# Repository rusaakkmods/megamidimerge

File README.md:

# rusaaKKMODS Megamidi Merge
================

A MIDI merge project for Arduino.

## Overview
-----------

This project is designed to merge MIDI input from multiple sources, calculate beats per minute (BPM), and update clock resolution as needed.

### Features
------------

* Merges MIDI input from two sources (MIDI-1 and MIDI-2)
* Calculates BPM from MIDI clock messages
* Updates clock resolution based on user input
* Displays current BPM, clock resolution, and master clock source on an OLED display

### Functions
-------------

* `initMidi()`: Initializes MIDI input and output interfaces.
* `calculateBPM()`: Calculates the current BPM from MIDI clock messages.
* `changeClockResolution()`: Updates the clock resolution based on user input.
* `readMidiInput()`: Reads and processes MIDI input from both sources.
* `printDisplay()`: Prints the current display information, including master clock source, BPM, and clock resolution.
* `isMasterInput1()`: Checks if the master clock source is set to MIDI-1.
* `loop()`: The main loop function that updates BPM, checks for user input, and reads MIDI input.

### Dependencies
------------

* Arduino library (for `millis()` and `digitalRead()` functions)
* MIDI library (for MIDI input and output handling)

### Hardware Requirements
----------------------

* Arduino board (e.g. Arduino Mega)
* MIDI input and output interfaces
* OLED display
* Push button for changing clock resolution

### Usage
-----

1. Upload the sketch to the Arduino board.
2. Connect the MIDI input and output interfaces to the board.
3. Connect the OLED display to the board.
4. Press the push button to change the clock resolution.

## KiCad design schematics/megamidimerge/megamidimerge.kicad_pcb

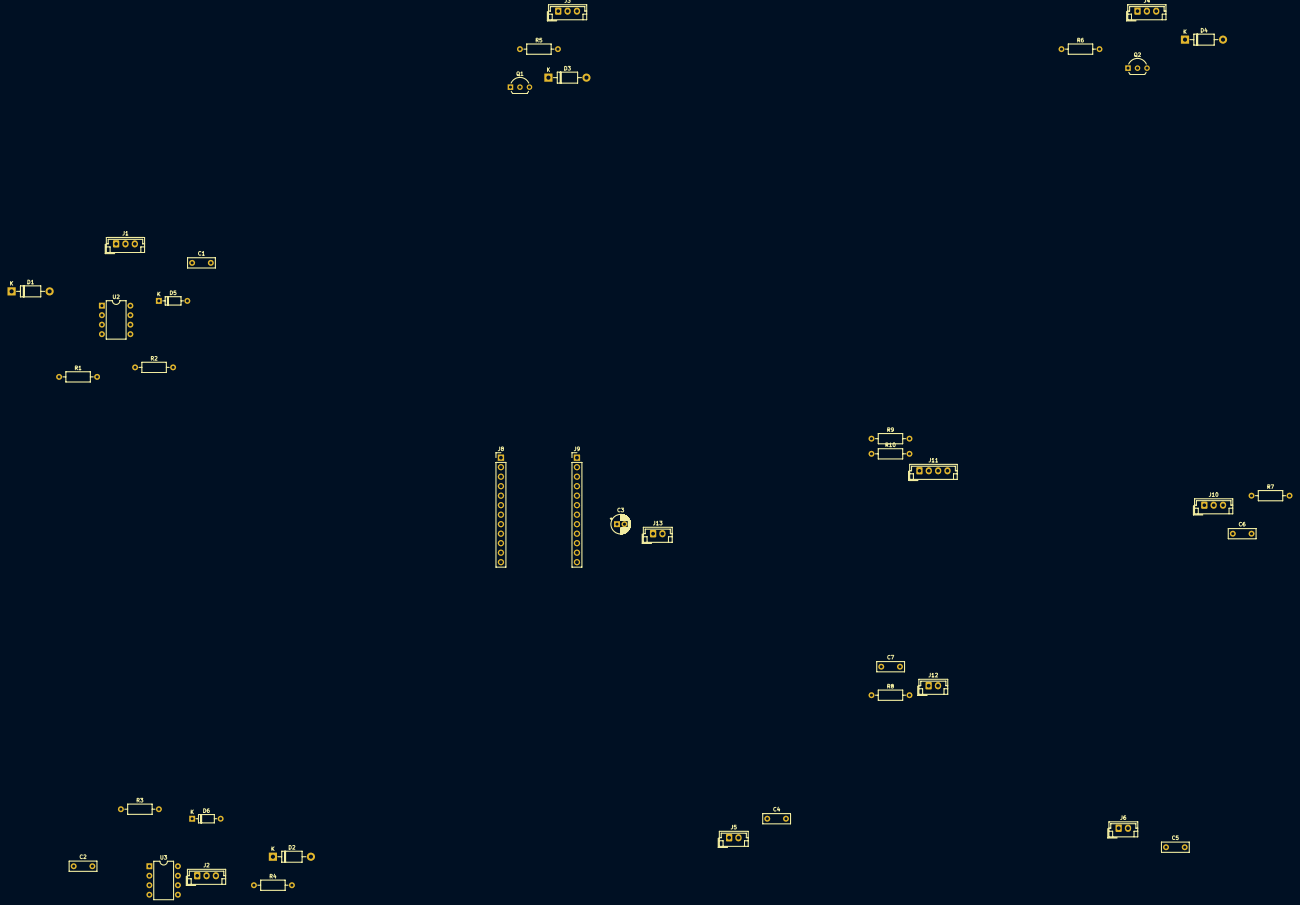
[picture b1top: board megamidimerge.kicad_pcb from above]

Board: 2 copper layers, 39 parts (0 on the bottom side), 24 nets, no tracks yet.

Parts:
C1, C2: 0.1uF; C_Rect_L7.2mm_W2.5mm_P5.00mm_FKS2_FKP2_MKS2_MKP2
C3: 10uF; CP_Radial_D5.0mm_P2.00mm
C4, C5, C6, C7: 10nF; C_Rect_L7.2mm_W2.5mm_P5.00mm_FKS2_FKP2_MKS2_MKP2
D1, D2, D3, D4: 1N5819; D_DO-41_SOD81_P10.16mm_Horizontal
D5, D6: 5.1V; D_DO-35_SOD27_P7.62mm_Horizontal
J1: MIDI IN 1; JST_EH_B3B-EH-A_1x03_P2.50mm_Vertical
J2: MIDI IN 2; JST_EH_B3B-EH-A_1x03_P2.50mm_Vertical
J3: MIDI OUT 1; JST_EH_B3B-EH-A_1x03_P2.50mm_Vertical
J4: MIDI OUT 2; JST_EH_B3B-EH-A_1x03_P2.50mm_Vertical
J5: CLOCK OUT 1; JST_EH_B2B-EH-A_1x02_P2.50mm_Vertical
J6: CLOCK OUT 2; JST_EH_B2B-EH-A_1x02_P2.50mm_Vertical
J8: LEFT; PinHeader_1x12_P2.54mm_Vertical
J9: RIGHT; PinHeader_1x12_P2.54mm_Vertical
J10: SWITCH MASTER; JST_EH_B3B-EH-A_1x03_P2.50mm_Vertical
J11: LCD; JST_EH_B4B-EH-A_1x04_P2.50mm_Vertical
J12: RESOLUTION; JST_EH_B2B-EH-A_1x02_P2.50mm_Vertical
J13: DC; JST_EH_B2B-EH-A_1x02_P2.50mm_Vertical
Q1, Q2: 2N2222; TO-92L_Inline_Wide
R1, R3, R5, R6: 220R; R_Axial_DIN0207_L6.3mm_D2.5mm_P10.16mm_Horizontal
R2, R4, R9, R10: 4.7K; R_Axial_DIN0207_L6.3mm_D2.5mm_P10.16mm_Horizontal
R7, R8: 10K; R_Axial_DIN0207_L6.3mm_D2.5mm_P10.16mm_Horizontal
U2, U3: 6N137; DIP-8_W7.62mm

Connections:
CLK1: C4.2, J5.2, J8.9
CLK2: C5.2, J6.2, J8.11
CPR: C7.1, J8.8, J12.1, R8.2
CSW: C6.1, J8.7, J10.2, R7.2
GND: C1.2, C2.2, C3.2, C4.1, C5.1, C6.2, C7.2, D3.2 (A), D4.2 (A), J1.3, J2.3, J3.3, J4.3, J5.1, J6.1, J8.3, J8.4, J9.2, J10.3, J11.1, J12.2, J13.2, Q1.3 (E), Q2.3 (E), R7.1, R8.1, U2.5 (GND), U3.5 (GND)
IN1: J8.2, R2.1, U2.6 (VO)
IN2: J8.10, R4.1, U3.6 (VO)
unnamed: D1.2 (A), J1.2, U2.3 (C)
unnamed: D1.1 (K), R1.2, U2.2 (A)
unnamed: D2.2 (A), J2.2, U3.3 (C)
unnamed: D2.1 (K), R3.2, U3.2 (A)
unnamed: D3.1 (K), J3.2, Q1.1 (C)
unnamed: D4.1 (K), J4.2, Q2.1 (C)
unnamed: D5.2 (A), J1.1
unnamed: D5.1 (K), R1.1
unnamed: D6.2 (A), J2.1
unnamed: D6.1 (K), R3.1
unnamed: Q1.2 (B), R5.2
unnamed: Q2.2 (B), R6.2
OUT1: J8.1, R5.1
OUT2: J9.9, R6.1
SCL: J8.6, J11.3, R10.2
SDA: J8.5, J11.4, R9.2
VCC: C1.1, C2.1, C3.1, J3.1, J4.1, J9.4, J10.1, J11.2, J13.1, R2.2, R4.2, R9.1, R10.1, U2.8 (VCC), U3.8 (VCC)

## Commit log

2024-11-06 initial working
2024-11-06 export to platformio
2024-11-06 add BPM
2024-11-06 add Pulse resolution
2024-11-08 update file structures
2024-11-08 remove too many readme
2024-11-10 update bak for improved non delay pulse
2024-11-10 updated with Clock In Detection Feature
2024-11-10 INPUT PULLUP instead
2024-11-10 refactor
2024-11-10 schematics
2024-11-11 schematic and review draft
2024-11-11 rename file arduino
2024-11-11 allow to sync to Gameboy LSDJ Slave Mode
2024-11-11 replace license
2024-11-11 commit license
2024-11-11 Update LICENSE
2024-11-11 upload prototype foto
2024-11-12 add summarize
2024-11-12 remove old
2024-11-15 add shcematics kicad
